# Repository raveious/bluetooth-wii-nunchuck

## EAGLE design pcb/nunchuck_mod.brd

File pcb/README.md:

# PCB Design

## Design Requirements

- [x] Has to fit in the case of the original, Nintendo Wii Nunchuck.
- [x] Battery powered.
- [x] Rechargable.
- [x] Bluetooth with a pretty decent range.
- [x] Power switch.

Extras:
- [ ] Act as a HID with 5 axes.
- [x] USB reprogrammable.
- [x] USB Charging.
- [x] Status LEDs.
- [ ] Report battery status over Bluetooth.
 - Use MAX17043

## Build of Materials

Part | Quantity | Description
:---|:---:|:---:

## References

- [Sparkfun Bluetooth Mate Gold](https://www.sparkfun.com/products/12580)
- [SparkFun LiPo Charger Basic - Mini-USB](https://www.sparkfun.com/products/10401)
- [SparkFun LiPo Fuel Gauge](https://www.sparkfun.com/products/10617)

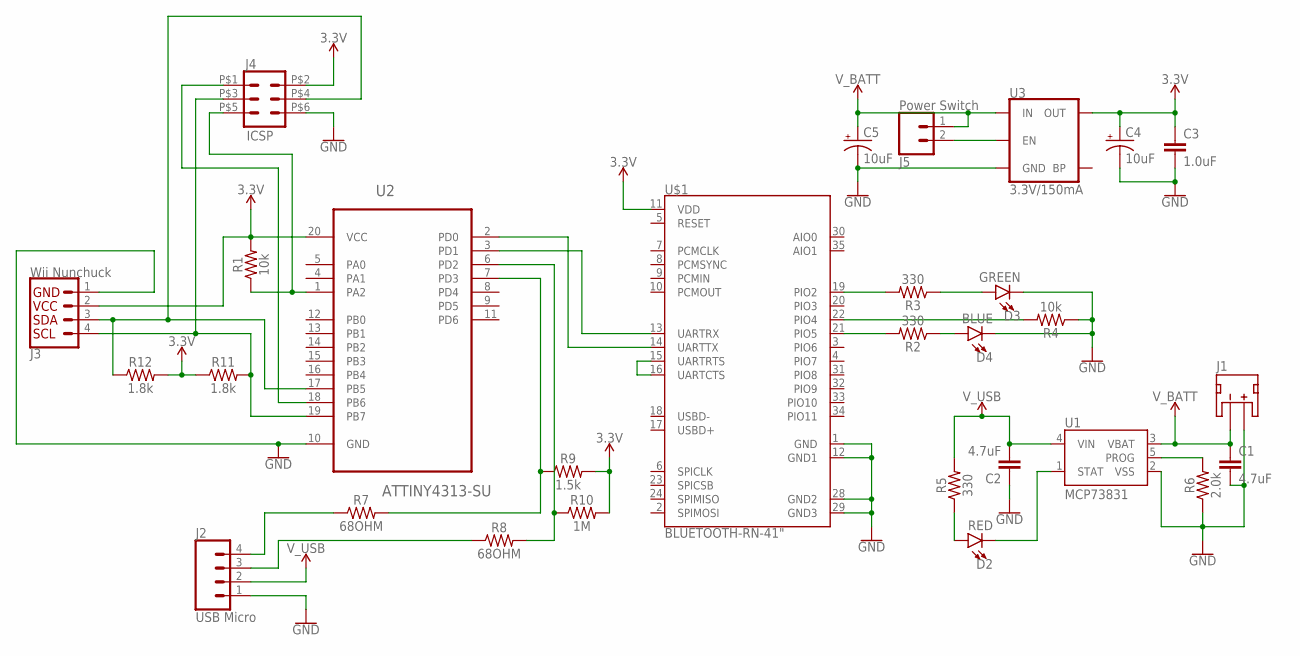
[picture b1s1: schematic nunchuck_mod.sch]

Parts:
C1, C2: 4.7uF; 0603
C3: 1.0uF; 0603
C4, C5: 10uF; 0603-POLAR
D2: RED; LED-0603
D3: GREEN; LED-0603
D4: BLUE; LED-0603
J1: JST_2MM_MALE; JST-2-SMD
J2: USB Micro; 1X04
J3: Wii Nunchuck; 1X04
J4: ICSP; 2X3_POGO
J5: Power Switch; 1X02
R1, R4: 10k; 0603
R2, R3, R5: 330; 0603
R6: 2.0k; 0603
R7, R8: 68OHM; 0603
R9: 1.5k; 0603
R10: 1M; 0603
R11, R12: 1.8k; 0603
U1: MCP73831; SOT23-5
U2: ATTINY4313-SU; SOIC127P1032X265-20N
U3: 3.3V/150mA; SOT23-5
U$1: BLUETOOTH-RN-41"; RN41

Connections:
3.3V: C3.1, C4.+, J3.2, J4.P$2 (2), R1.2, R9.2, R10.2, R11.1, R12.2, U2.20 (VCC), U3.5 (OUT), U$1.11 (VDD)
GND: C1.2, C2.1, C3.2, C4.-, C5.-, D3.C, D4.C, J1.2 (+), J2.1, J3.1, J4.P$6 (6), R4.1, R6.1, U1.2 (VSS), U2.10 (GND), U3.2 (GND), U$1.1 (GND), U$1.12 (GND1), U$1.28 (GND2), U$1.29 (GND3)
unnamed: R3.2, U$1.19 (PIO2)
unnamed: R4.2, U$1.22 (PIO4)
unnamed: R2.2, U$1.21 (PIO5)
unnamed: D4.A, R2.1
unnamed: D3.A, R3.1
unnamed: U2.2 (PD0), U$1.14 (UARTTX)
unnamed: U2.3 (PD1), U$1.13 (UARTRX)
unnamed: U$1.15 (UARTRTS), U$1.16 (UARTCTS)
unnamed: D2.A, R5.1
unnamed: R6.2, U1.5 (PROG)
unnamed: R8.2, R10.1, U2.6 (PD2)
unnamed: J5.2, U3.3 (EN)
unnamed: J3.4, J4.P$3 (3), R11.2, U2.19 (PB7)
unnamed: D2.C, U1.1 (STAT)
unnamed: R7.2, R9.1, U2.7 (PD3)
unnamed: J2.4, R7.1
unnamed: J2.3, R8.1
unnamed: J4.P$5 (5), R1.1, U2.1 (PA2)
unnamed: J3.3, J4.P$4 (4), R12.1, U2.17 (PB5)
unnamed: J4.P$1 (1), U2.18 (PB6)
V_BATT: C1.1, C5.+, J1.1 (-), J5.1, U1.3 (VBAT), U3.1 (IN)
V_USB: C2.2, J2.2, R5.2, U1.4 (VIN)

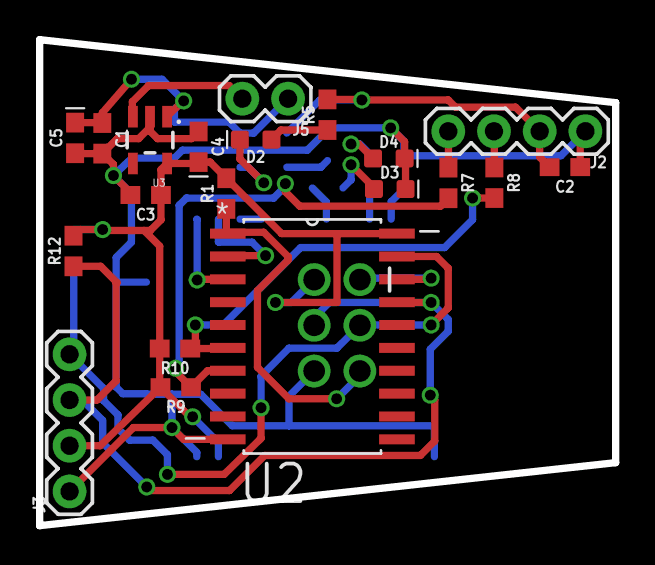
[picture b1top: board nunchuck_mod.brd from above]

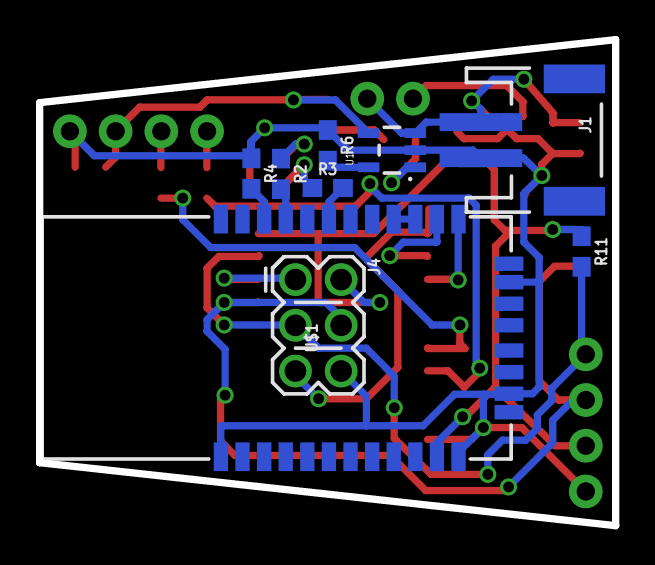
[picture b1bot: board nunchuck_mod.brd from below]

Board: 2 copper layers, 32.0 x 27.0 mm, 29 parts (9 on the bottom side), 24 nets.

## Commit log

2017-02-16 Adding eagle stuff to .gitignore
2017-03-04 Adding in mod progress
    Still missing a LDO regulator and need to do the PCB design itself.
2017-03-06 Completed PCB design
    Had to replace RGB led with 3 individual LEDs and completed PCB design
2019-02-02 Adding in some docs that I forgot to push

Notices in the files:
parts and their libraries:
SparkFun-Capacitors: Licensing: Creative Commons ShareAlike 4.0 International - https://creativecommons.org/licenses/by-sa/4.0
